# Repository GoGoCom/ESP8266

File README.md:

# Welcome to ESP8266 Lecture

Welcome to YouTube Lecture for ESP8266 

## [Contents](https://youtu.be/eRAwDwjtinM)
### 1. Fundamental Class
- [ARDUINO Basic Environment Setting](https://youtu.be/JNd7XEw42ps)
- [ARDUINO Program Running & Debugging](https://youtu.be/F_9_j-7GvK8)
- ARDUINO C/C++ 
  - [Variable](https://youtu.be/Owym6XwLJYU)
  - [Array & Pointer](https://youtu.be/r_iqjg1brbg)
  - [Operator](https://youtu.be/Ua6nBRjVqdc)
  - [Flow Control](https://youtu.be/5EHK0ps3G9E)
  - [Compile](https://youtu.be/Ue2AbuZHpxg)
  - C++ 
    - [Class & Object](https://youtu.be/ICh2nTJk29E)
    - [Inheritance & Polymorphism](https://youtu.be/aynaNYOh_2A)
### 2. Hardware Operation Experience
- [Relay](https://youtu.be/CpzohTQOwz0)
- [Buzzer](https://youtu.be/HYZvMa8oElU)
- Temperature Sensor
   - [DHT22](https://youtu.be/7DIk08-u8mo)
   - [DS18B20](https://youtu.be/A37lg_PZiYQ)
- [LED WS2812B Neopixel](https://youtu.be/egXmU_p3yb4)
- [I2C  OLE Display](https://youtu.be/r0wPfdEN5Kc)
- [Bluetooth](https://youtu.be/iZtiVULcuNY)
### 3. ESP8266 Internal Experience
- [EEPROM](https://youtu.be/tGPL5mgSFMA)
- [WiFi](https://youtu.be/SWkVqtEi31I)
- [Web Server](https://youtu.be/wZ4dsRRwKvI)
- [Web Client(Internet Time)](https://youtu.be/y0UTOy235Ro)
- [HTML](https://youtu.be/bG98dAQHwlE)
- [HTML Style](https://youtu.be/3LWX76T2IRs)
- [HTML Form](https://youtu.be/YaudaPLHNSY)
- [Input](https://youtu.be/aZVZsw9s3SQ)
- [SPIFF(External CSS)](https://youtu.be/pah9Q4-66N0)
- [WiFi Mode, Login Security, mDNS ](https://youtu.be/2dJ5J6udtos)
### 4. Internet Communication
- [MQTT](https://youtu.be/dg9xWJVtsxE)
- [Node-Red Install](https://youtu.be/jh07Kp2tbMs)
- [Node-Red Running](https://youtu.be/tIFlVYCLw4Q)
- [EST8266MQTT PubSubClient](https://youtu.be/WKgMdtCtdro)
- [EST8266MQTT NodeRed](https://youtu.be/IHJE5lQI7mk)
- [Temperature, Humidity, Relay Operation](https://youtu.be/OLOFtsrPGGc)
- [Jason](https://youtu.be/FlilQ9nkO4I)
- [Port Forward , DDNS](https://youtu.be/IMViN0QGAvY)
### 5. DIY - WiFiSwitch
- [Circuit, PCB,Program, Case Design(3D printing)](https://youtu.be/RDv5FjHP5Xo)
- [Bluetooth](https://youtu.be/QulaJZXTUxg)
- [JSON, FRED, MQTT](https://youtu.be/aZn0C2d3mKg)
### 6. Blynk
- [Introduction of Blynk](https://youtu.be/o-JLenDly64)
- [Blynk - Heater](https://youtu.be/stAkdMGl5TU)
### 7. Voice Control
- [Introduction of IFTTT, Google Assitant and Adafruit](https://youtu.be/3wgT0iNDrnI)
- [Preparation Video for Voice Control](https://youtu.be/-zy5h0WDZeI)
- [Connection with Adafruit, IFTTT, Google Assitant for Voice Control](https://youtu.be/SLS5ZYJJiXQ)
- [Connection  Video for Voice Control](https://youtu.be/6ugJ0UG34hE)
### 8. Blynk Multi projects
- [Introduction of Multi project](https://youtu.be/5t2xtHF2-xQ)
### 9. Blynk WeMos D1 Mini
- [DHT22, Relay, BM180, L3G, LSM303 - Barometer, Accelerometer, magnetic Sensor](https://youtu.be/RBmRkGXUNWs)

## [Our Website](https://GoGoCom.github.io/)
## [YouTube WiFiStwitch](https://youtu.be/H9YjLBqm_VE)
# Thank you so much!

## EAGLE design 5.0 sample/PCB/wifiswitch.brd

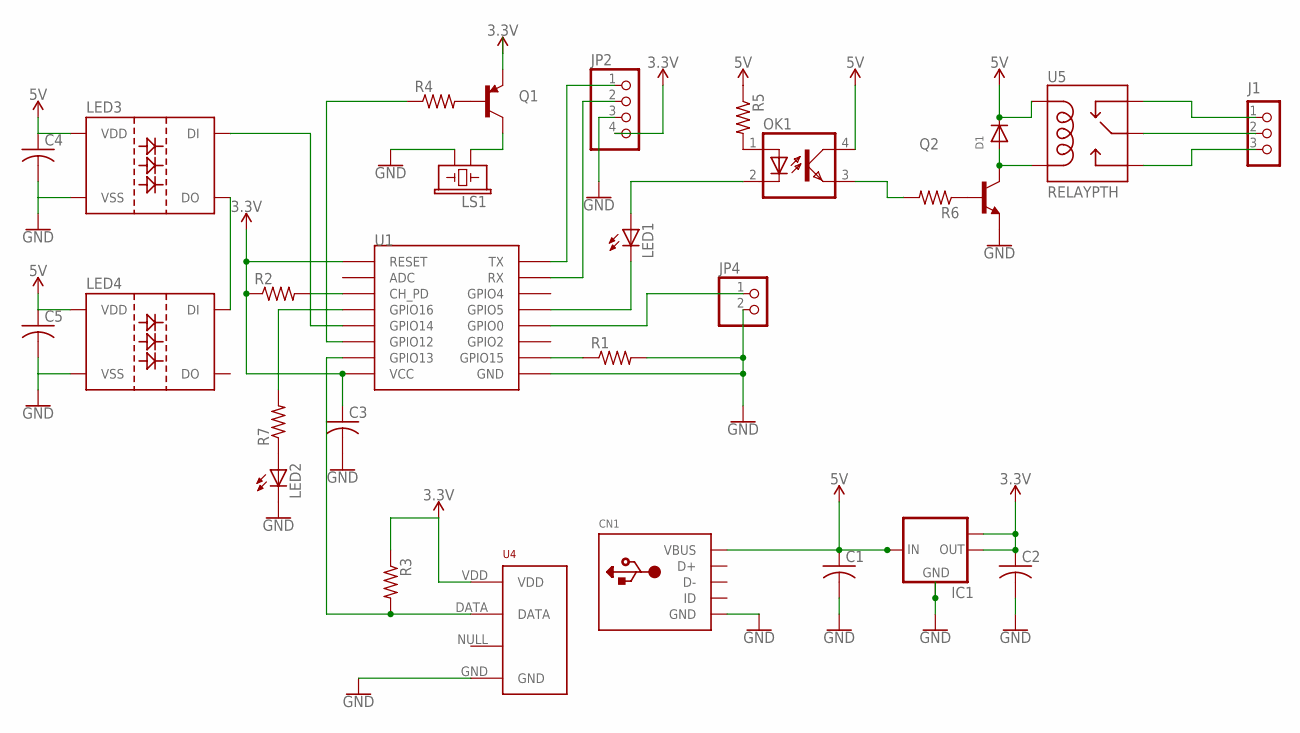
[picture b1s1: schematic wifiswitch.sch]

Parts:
C1, C2: C-USC0805; C0805
C3, C4, C5: C-USC0805; C0805; MPN C0805X104J5RAC3316
CN1: USBTHM; USB-MINIB-THM
D1: DIODESOD-123; SOD-123
IC1: LM1117IMPX-3.3; SOT223; MPN ADP3339AKCZ-3.3-R7
J1: CON_TERMINAL_BLOCK_03-5MM; TERMINAL_BLOCK_3P_5
JP2: PINHD-1X4; 1X04
JP4: PINHD-1X2; 1X02
LED1, LED2: LEDCHIP-LED0805; CHIP-LED0805
LED3, LED4: WS2812B
LS1: BUZZER-PTH; BUZZER-12MM
OK1: PC817; DIL04
Q1: TRANSISTOR_PNPPMBT3906; SOT23-3
Q2: TRANSISTOR_BJT_NPN-SOT-23-BEC; SOT-23
R1, R2, R3, R4, R5, R6, R7: R-US_R0805; R0805
U1: ESP12SMD; ESP12-SMD
U4: RHT03_DHT-22_AM2302RA; RHT03_DHT-22/RA
U5: RELAYPTH; SRD-05VDC-SL-C

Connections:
3.3V: C2.1, C3.1, IC1.2 (OUT), IC1.TAB (OUT1), JP2.4, Q1.2 (E), R2.1, R3.1, U1.RESET, U1.VCC, U4.VDD
5V: C1.1, C4.1, C5.1, CN1.VBUS, D1.C, IC1.3 (IN), LED3.1 (VDD), LED4.1 (VDD), OK1.4 (COL), R5.1, U5.P$1 (COIL1)
GND: C1.2, C2.2, C3.2, C4.2, C5.2, CN1.GND, IC1.1 (GND), JP2.3, JP4.2, LED2.C, LED3.3 (VSS), LED4.3 (VSS), LS1.- (2), Q2.2 (E), R1.2, U1.GND, U4.GND
unnamed: LS1.+ (1), Q1.3 (C)
unnamed: R1.1, U1.GPIO15
unnamed: LED3.4 (DI), U1.GPIO14
unnamed: R4.1, U1.GPIO12
unnamed: R3.2, U1.GPIO13, U4.DATA
unnamed: LED2.A, R7.1
unnamed: LED1.A, OK1.2 (C)
unnamed: JP2.1, U1.TXD0 (TX)
unnamed: JP4.1, U1.GPIO0
unnamed: Q2.1 (B), R6.1
unnamed: JP2.2, U1.RXD0 (RX)
unnamed: R2.2, U1.CH_PD
unnamed: Q1.1 (B), R4.2
unnamed: OK1.1 (A), R5.2
unnamed: D1.A, Q2.3 (C), U5.P$4 (COIL0)
unnamed: J1.1, U5.P$5 (SWCLOSE)
unnamed: J1.2, U5.P$3 (SWCOMMON)
unnamed: J1.3, U5.P$2 (SWOPEN)
unnamed: OK1.3 (EMIT), R6.2
unnamed: LED1.C, U1.GPIO5
unnamed: LED3.2 (DO), LED4.4 (DI)
unnamed: R7.2, U1.GPIO16

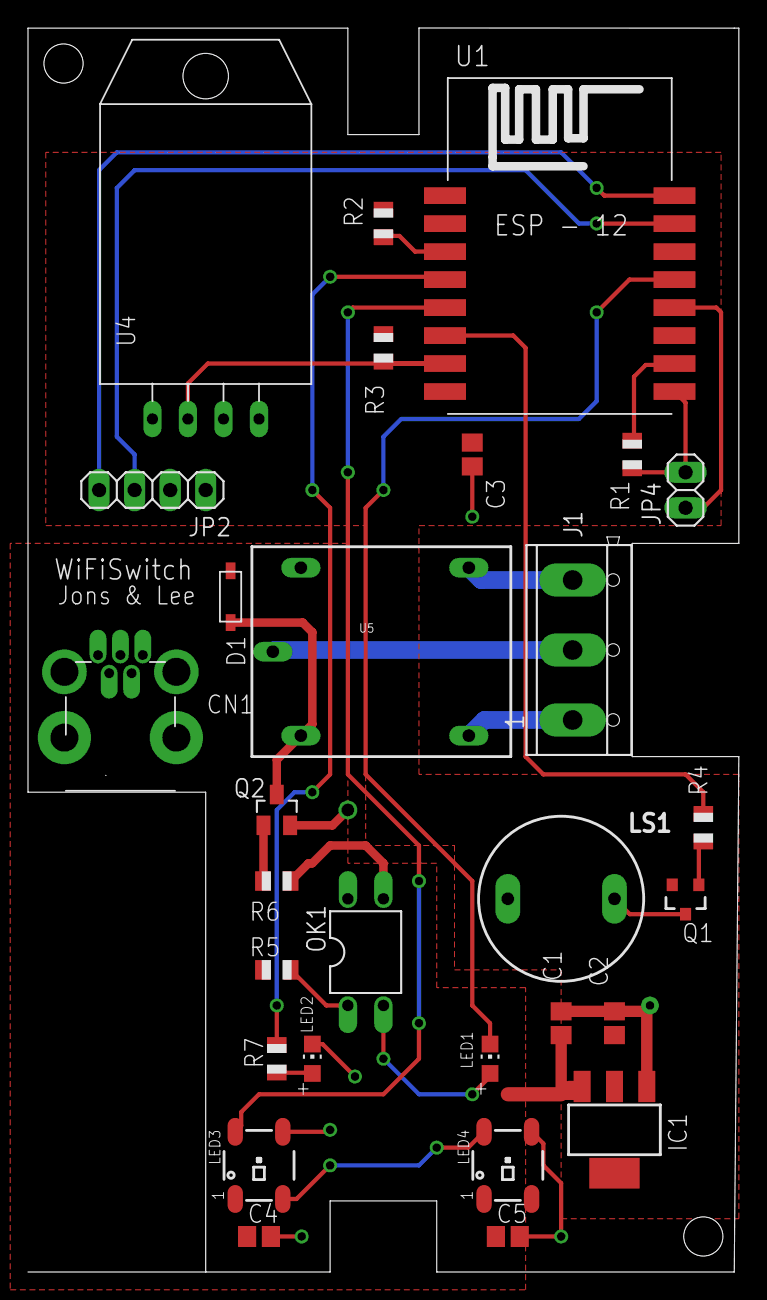
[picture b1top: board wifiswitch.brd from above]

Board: 2 copper layers, 50.8 x 88.9 mm, 29 parts (0 on the bottom side), 25 nets.

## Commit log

2019-09-18 Create ._HM10 Serial
2019-09-18 Create ._HM10 SerialTests
2020-01-04 Create LICENSE

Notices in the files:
parts and their libraries:
SparkFun-Electromechanical: Licensing: Creative Commons ShareAlike 4.0 International - https://creativecommons.org/licenses/by-sa/4.0
